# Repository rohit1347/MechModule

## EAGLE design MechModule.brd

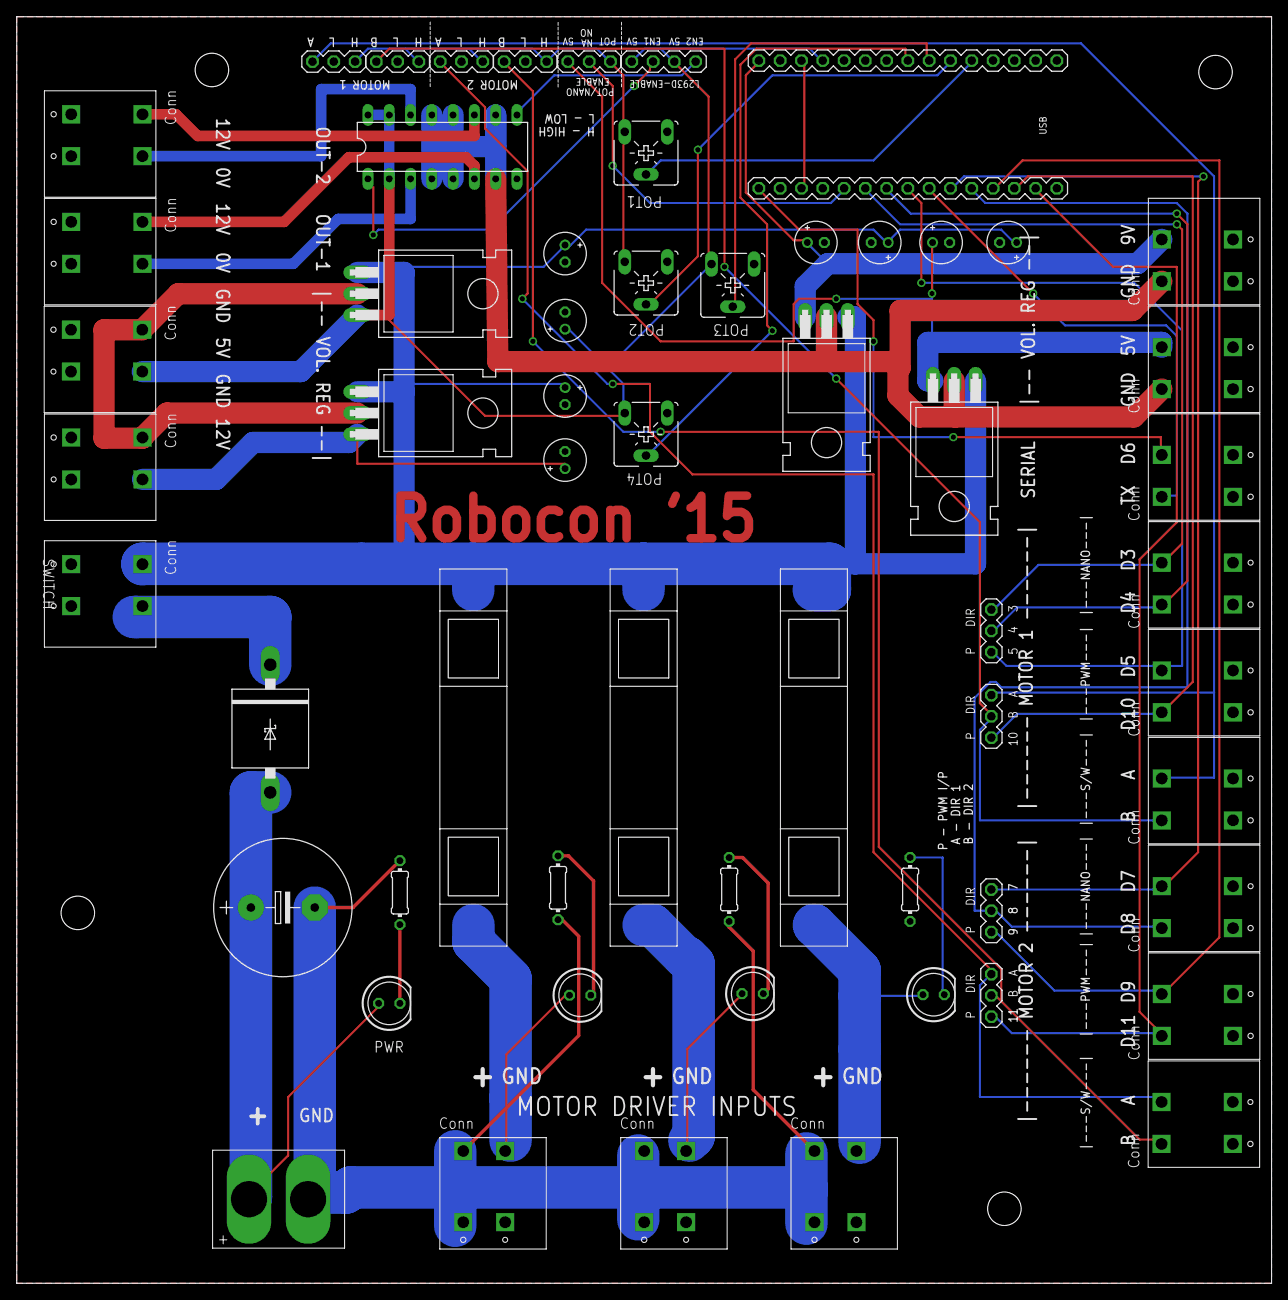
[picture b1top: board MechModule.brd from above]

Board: 2 copper layers, 149.7 x 151.1 mm, 59 parts (0 on the bottom side), 42 nets.

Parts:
5V1, 5V2, 9V, 12V: SCREWCONN; STANDARD
C1, C2, C4, C5, C8, C9, C12, C13: E2-5
C14: E7,5-16
D1: P6T15
DCV: MA04-1
EN-NANO: MA03-1
FUSE1, FUSE2, FUSE3: CPT-FUSE; CPT-FUSES
IC1, IC2: 7805; 78XX
IC3: 7812; 78XX
IC5: 7809; 78XX
IC6: L293D; DIL16
LIPO: SCREW_XT-60
M1, M2, M3: LED5MM
M1D1, M1D2, M1H, M1S, M2D1, M2D2, M2H, M2S: MA03-1
M1DH, M1DS, M1P, M2DH, M2DS, M2P: SCREWCONN; STANDARD
MD1, MD2, MD3: SCREWCONN; STANDARD
NANO: ARD-NANO
OUT1, OUT2: SCREWCONN; STANDARD
POT1, POT2, POT3, POT4: CA6V
PWR: LED5MM
R1, R3, R4, R5: 0204/7
SERIAL: SCREWCONN; STANDARD
SWITCH: SCREWCONN; STANDARD

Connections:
5V: 5V2.3, C5.+, DCV.1, DCV.3, IC1.3, IC6.2, IC6.15, IC6.16, NANO.5V, POT3.E, POT4.E
5VA: 5V1.3, C1.+, EN-NANO.1, IC2.3
5VB: EN-NANO.3, M1D1.3, M1D2.3, M2D1.3, M2D2.3, POT1.E, POT2.E
9V: 9V.3, C8.+, IC5.3, NANO.VIN
+24: C14.+, D1.A, LIPO.P$1, PWR.A
A1: NANO.A1, POT1.S
A2: NANO.A2, POT2.S
A3: NANO.A3, POT3.S
A4: NANO.A4, POT4.S
D2: EN-NANO.2, NANO.D2
D3: M1DS.3, M1S.1, NANO.D3
D4: M1DS.4, M1S.2, NANO.D4
D5: M1P.3, M1S.3, NANO.D5
D6: NANO.D6, SERIAL.4
D7: M2DS.3, M2S.1, NANO.D7
D8: M2DS.4, M2S.2, NANO.D8
D9: M2P.3, M2S.3, NANO.D9
D10: M1H.3, M1P.4, NANO.D10
D11: M2H.3, M2P.4, NANO.D11
EN1: DCV.2, IC6.1
EN2: DCV.4, IC6.9
FUSE1: FUSE1.P$1, M1.A, MD1.3
FUSE2: FUSE2.P$1, M2.A, MD2.3
FUSE3: FUSE3.P$1, M3.A, MD3.3
GND: 5V1.4, 5V2.4, 9V.4, 12V.4, C1.-, C2.-, C4.-, C5.-, C8.-, C9.-, C12.-, C13.-, C14.-, IC1.2, IC2.2, IC3.2, IC5.2, IC6.4, IC6.5, IC6.7, IC6.10, IC6.12, IC6.13, LIPO.P$2, M1D1.2, M1D2.2, M2D1.2, M2D2.2, MD1.4, MD2.4, MD3.4, NANO.GND1, NANO.GND2, POT1.A, POT2.A, POT3.A, POT4.A, R1.1, R3.1, R4.1, R5.1
M1D1: M1D1.1, M1DH.3, M1H.1
M1D2: M1D2.1, M1DH.4, M1H.2
M2D1: M2D1.1, M2DH.3, M2H.1
M2D2: M2D2.1, M2DH.4, M2H.2
unnamed: D1.C, SWITCH.3
unnamed: M3.K, R1.2
unnamed: M2.K, R3.2
unnamed: M1.K, R4.2
unnamed: PWR.K, R5.2
OUTA1: IC6.3, OUT1.3
OUTA2: IC6.6, OUT1.4
OUTA3: IC6.14, OUT2.3
OUTA4: IC6.11, OUT2.4
RESET: NANO.RST1, NANO.RST2
S$1: 12V.3, C12.+, IC3.3
TX: NANO.TX, SERIAL.3
VCC: C2.+, C4.+, C9.+, C13.+, FUSE1.P$2, FUSE2.P$2, FUSE3.P$2, IC1.1, IC2.1, IC3.1, IC5.1, SWITCH.4
